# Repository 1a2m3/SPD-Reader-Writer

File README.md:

# SPD-RW
Arduino-based SPD Reader/Writer with Reversible Software Write Protection capabilities

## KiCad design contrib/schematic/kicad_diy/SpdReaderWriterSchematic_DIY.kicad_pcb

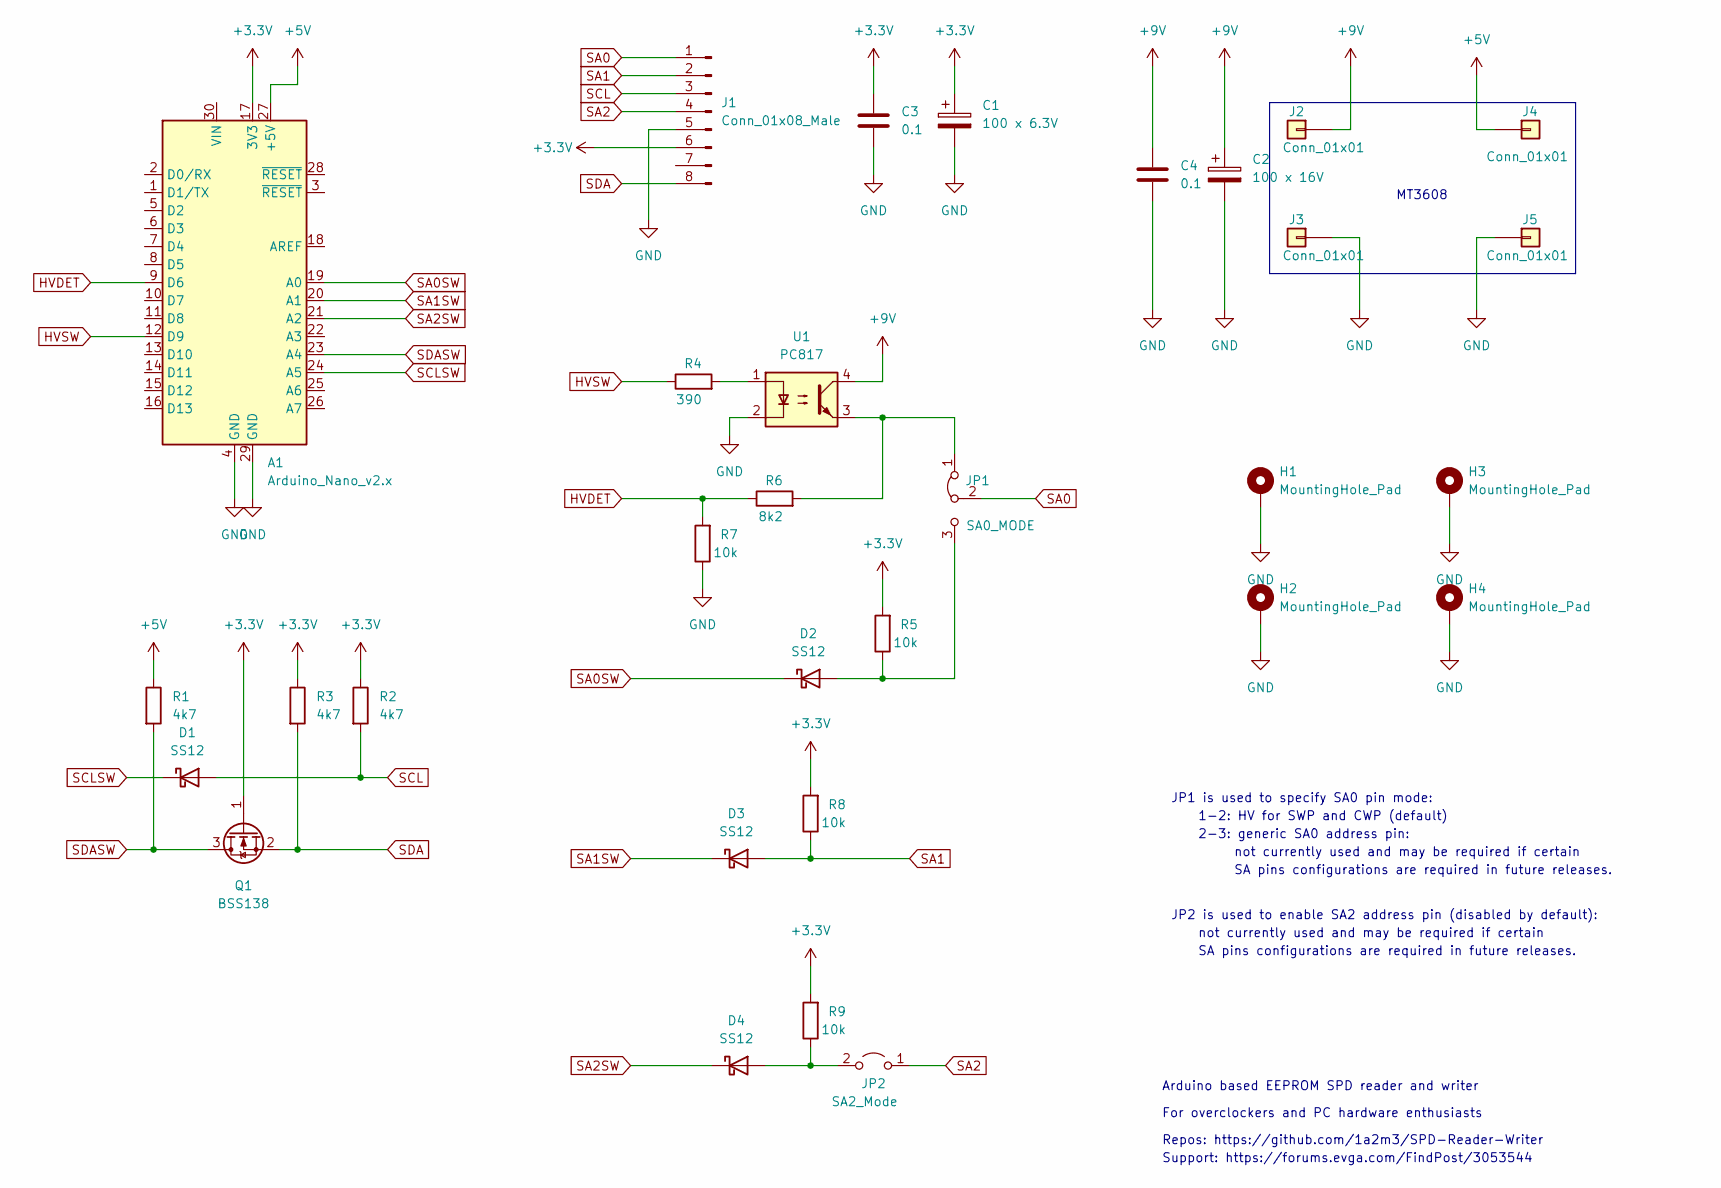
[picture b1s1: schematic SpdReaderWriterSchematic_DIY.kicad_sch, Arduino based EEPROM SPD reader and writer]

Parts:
A1: Arduino_Nano_v2.x; Arduino_Nano
C1: 100 x 6.3V; CP_Radial_D5.0mm_P2.00mm
C2: 100 x 16V; CP_Radial_D5.0mm_P2.00mm
C3, C4: 0.1; C_0805_2012Metric
D1, D2, D3, D4: SS12; D_SMA
H1, H2, H3, H4: MountingHole_Pad; MountingHole_3.2mm_M3_Pad
J1: Conn_01x08_Male; PinHeader_1x08_P2.54mm_Vertical
J2, J3, J4, J5: Conn_01x01; Pin_D1.0mm_L10.0mm_LooseFit
JP1: SA0_MODE; PinHeader_1x03_P2.54mm_Vertical
JP2: SA2_Mode; PinHeader_1x02_P2.54mm_Vertical
Q1: BSS138; SOT-23
R1, R2, R3: 4k7; R_0805_2012Metric
R4: 390; R_0805_2012Metric
R5: 10k; R_1206_3216Metric
R6: 8k2; R_0805_2012Metric
R7, R8, R9: 10k; R_0805_2012Metric
U1: PC817; DIP-4_W7.62mm

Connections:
+3.3V: A1.17 (3V3), C1.1, C3.1, J1.6, Q1.1 (G), R2.1, R3.1, R5.2, R8.2, R9.2
+5V: A1.27 (+5V), J4.1, R1.1
+9V: C2.1, C4.1, J2.1, U1.4
GND: A1.4 (GND), A1.29 (GND), C1.2, C2.2, C3.2, C4.2, H1.1, H2.1, H3.1, H4.1, J1.5, J3.1, J5.1, R7.1, U1.2
HVDET: A1.9 (D6), R6.1, R7.2
HVSW: A1.12 (D9), R4.1
unnamed: D2.2 (A), JP1.3 (B), R5.1
unnamed: D4.2 (A), JP2.2 (B), R9.1
unnamed: JP1.1 (A), R6.2, U1.3
unnamed: R4.2, U1.1
SA0: J1.1, JP1.2 (C)
SA0SW: A1.19 (A0), D2.1 (K)
SA1: D3.2 (A), J1.2, R8.1
SA1SW: A1.20 (A1), D3.1 (K)
SA2: J1.4, JP2.1 (A)
SA2SW: A1.21 (A2), D4.1 (K)
SCL: D1.2 (A), J1.3, R2.2
SCLSW: A1.24 (A5), D1.1 (K)
SDA: J1.8, Q1.2 (S), R3.2
SDASW: A1.23 (A4), Q1.3 (D), R1.2

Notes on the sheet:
JP2 is used to enable SA2 address pin (disabled by default):
MT3608
not currently used and may be required if certain
SA pins configurations are required in future releases.
1-2: HV for SWP and CWP (default)
Arduino based EEPROM SPD reader and writer
2-3: generic SA0 address pin:
Repos: https://github.com/1a2m3/SPD-Reader-Writer
Support: https://forums.evga.com/FindPost/3053544
For overclockers and PC hardware enthusiasts
JP1 is used to specify SA0 pin mode:

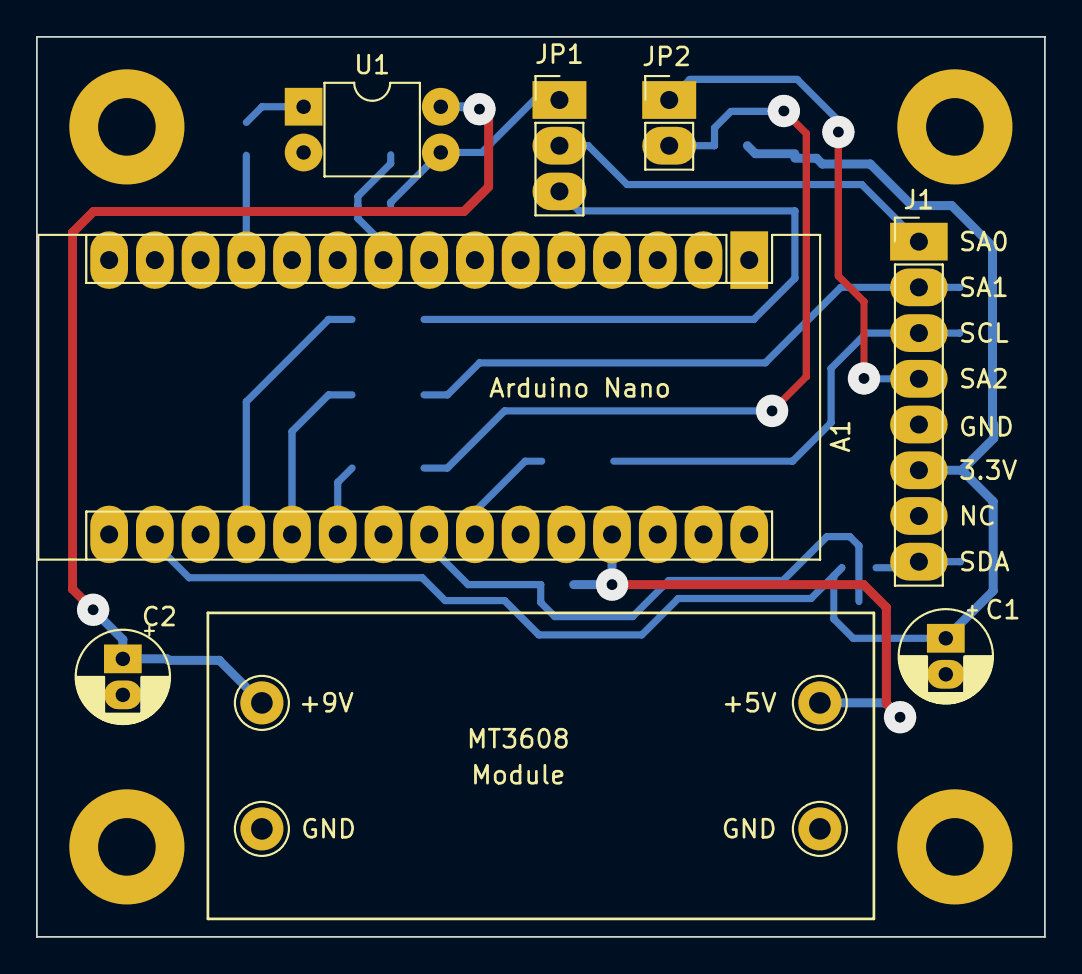
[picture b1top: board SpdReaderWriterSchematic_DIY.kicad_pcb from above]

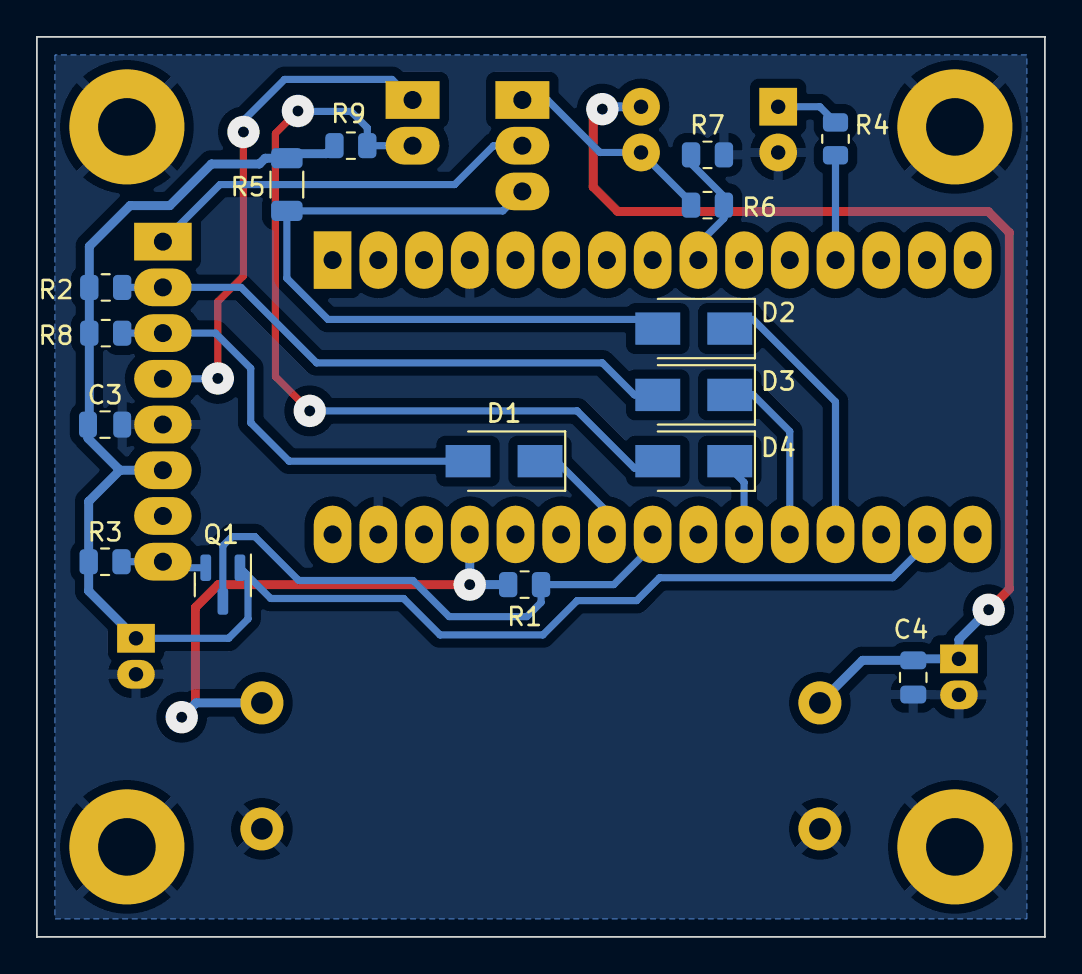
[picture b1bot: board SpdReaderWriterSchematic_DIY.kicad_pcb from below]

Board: 2 copper layers, 56.0 x 50.0 mm, 31 parts (16 on the bottom side), 20 nets.

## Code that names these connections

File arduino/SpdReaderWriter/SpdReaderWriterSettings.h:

#define PORT      Serial   // Communications Port, default is "Serial". Change to "SerialUSB" for native USB Arduinos (Leonardo, Micro, Due, Yun, etc)
#define BAUD_RATE 115200   // Serial port baud rate, must match program's serial baud rate
#define HVSW      6        // High Voltage (Optocoupler) switch pin number
#define SA0SW     2        // SA0 select pin number
#define SA1SW     3        // SA1 select pin number
#define SA2SW     4        // SA2 select pin number

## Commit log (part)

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2022-11-09 Formatting
2022-11-09 Byte array search
2022-11-09 GUI Screenshot
    New editor
2022-11-10 Cleanup
    LINQ looks cleaner :)
2022-11-10 SPD update
2022-11-10 SPD5 info and checks
2022-11-10 FW cleanup
    Firmware cleanup and update
2022-11-10 ID database update
    Jedec Manufacturers' IDs database update
2022-11-18 Compiler fix
    Fixed compiler to include SPD classes
2022-11-20 Smbus and driver improvements
    Improved Smbus and driver performance, cleanup
2022-12-09 Cleanup
2022-12-09 Improved stability
2022-12-15 Driver refactoring
2022-12-15 Cleanup and refactoring
2022-12-15 Added trim byte array + refactoring
2022-12-15 SPD refactoring, cleanup
    Crc validation, data types refactoring, cleanup
2022-12-15 File location fix
2022-12-19 Refactor, cleanup
2022-12-19 Alert updates
2022-12-19 SPD refactoring, cleanup, CRC updates
2022-12-19 P/N cleanup, Id fix
2022-12-21 Byte array and gzip updates
    Added byte array compare, gzip peek and performance improvements
2022-12-21 FW version info, refactoring
    Added included FW version info, refactoring and cleanup
2022-12-27 Array functions
2022-12-27 Compatibility update, cleanup
2022-12-27 AMD Expo CRC
    Added AMD Expo CRC validation
2022-12-28 Encoding
    Removed UTF-8 BOM
2022-12-30 Validation
    Data length validation
2022-12-30 Cleanup + Expo
    Added AMD Expo signature, some cleanup
2022-12-30 Cleanup
    Cleanup, added WP description
2022-12-30 Compatibility and performance
    Linq is slower for large file comparison, thus is gone
2022-12-30 Added length and P/N
    Added length and Part Number types
2022-12-30 Performance and cleanup
2022-12-30 Fixed compiler warnings
2023-01-01 New screenshot
2023-01-03 More cleanup
    Code decluttering, thanks to generics
2023-01-04 Refactoring, cleanup
2023-01-06 Data refactoring
2023-01-06 Driver behavior fixed
    Fixes driver extracting when running as normal user, and driver not stopping on exit.
2023-01-09 Improved reliability
2023-01-09 DDR5 RSWP
2023-01-13 Fixed DDR5 info
    Fixed DDR5 SPD manufacturer name detection
2023-01-13 Arrays, cleanup
2023-01-14 SPD5 hub & DDR5 support, cleanup
2023-01-14 Refactoring and cleanup
2023-01-14 Compatibility, checks, branding
2023-01-14 Array contains method
2023-01-14 Cleanup and color option
2023-01-14 Fixed warnings
    Fixed warnings CS0660 and CS0661
2023-01-15 Improvements and smbus fix
    Improved reading performance, fixed smbus bus # bug, added smbus exceptions, code cleanup
2023-01-15 Block check
2023-01-16 Improved performance
2023-01-16 Refactoring
2023-01-19 Cleanup, Alert time
2023-01-19 Name, cleanup
2023-01-19 Array functions, cleanup
2023-01-19 FW check, cleanup
2023-01-19 Subarray
2023-01-20 Path and switches compatibility
    File path and output modifier switches compatibility
2023-01-20 Scan fix
2023-01-25 DDR5 support
2023-01-25 Update RSWP on hot swap
2023-01-26 Outdated schematic
2023-01-26 Write protection improvement
    improved RSWP tests
2023-01-27 Pin config, cleanup
2023-01-28 Generics, cleanup
2023-01-31 Performance, protocol, cleanup
    Improved performance, added new protocol support, added generics, cleanup
2023-01-31 Refactoring
    Moved SpdReaderWriterDll to SpdReaderWriterCore namespace
2023-02-02 Better performance and stability
    Improved performance and stability, cleanup, and refactoring
2023-02-02 Byte array to hex string
2023-02-02 20230202 screenshot
    Version 20230202 screenshot showing DDR5 support
2023-02-03 EEPROM page set fix
2023-02-03 Improved spd size
2023-02-03 Improved performance and stability
2023-02-05 DDR5 test
2023-02-05 DDR5 support, protocol update
2023-02-05 Updated FW
2023-02-05 Improved stability, added DDR5 support
2023-03-09 Fixes inaccessible smbus on some systems
2023-03-09 Improved performance and reliability
2023-05-06 Object array, cleanup
2023-05-06 Pci info
2023-05-06 Intel 600/700 support
2023-05-06 Write test, Cleanup
2023-06-09 WP compatibility
    Write protection compatibility update for SDR-DDR4
2023-08-05 Smbus DDR5 RSWP support
    Added Smbus DDR5 RSWP detection
2023-09-14 Update Data.cs
    Updated object array converter to support nested arrays
2023-09-14 Update Data.cs
    One numeric data check
2023-09-14 Update Data.cs
    Fix for nested arrays
2023-09-15 Update Arduino.cs
    Refactoring, SPD5 hub RSWP verification
2023-09-19 Extended BDC functions + fixed CompareArray()
    Extended BDC functions to work with any type of numeric input;
    Added array size check to CompareArray
2023-09-19 Removed WinRing0 files
2023-09-23 Data size, fixed BCD
2023-09-23 Hardware IDs enums
2023-09-23 Total refactoring
2023-09-23 Not needed
2023-09-23 SPD5 hub write verification
2023-09-24 Memory read, cleanup
2023-09-24 Driver & Firmware updated
    Replaced WinRing0 driver with CPUID CPUZ driver
2023-09-24 Cleanup
    Removed unused device
2023-09-24 Improved write protection test
2023-09-24 Cleanup :)
    That
    extra
    line
    bothered
    me
2023-09-27 Added CloseHandle
2023-09-27 Improved stability and performance
2023-09-29 Refactoring for consistency
2023-09-29 Process and assembly name
2023-09-29 Cleanup, error codes
2023-09-30 Improved stability, cleanup
2023-09-30 Fixed access modifiers
2023-10-12 Cleanup
    removed cpuz driver files
2023-10-12 Improved AMD smbus detection
2023-10-29 Cleanup, refactoring
2023-11-01 Improved random arrays
2023-11-18 Vendor ID DB update
    ID codes database update (ref. JEP106BH, Sept 2023)
2023-12-02 added VIA smbus, refactoring
    Added VIA chipsets smbus support
2023-12-05 VIA updates
    Improved VIA smbus support
2023-12-05 Protocol update, cleanup
2023-12-05 ASCII updates
2023-12-05 P/N checks
2023-12-05 Compatibility update
2023-12-06 X299 fix
    fix for Skylake-X smbus
2023-12-06 protocol update, improved ddr5 compatibility
2023-12-08 Added baud rate option, improved stability
2023-12-08 PMIC validation, cleanup
2023-12-08 FW update
    ver 20231207
2023-12-08 pmic address validation
2023-12-08 X299 smbus status + general cleanup
2023-12-08 exe assembly version
2023-12-08 Help & input validation
    Updated help, improved user input validation
2023-12-08 port validation
2023-12-08 Admin, versions updates
2023-12-09 device interface
2023-12-09 dll versions
2023-12-09 screenshots
2023-12-09 new screenshots
    New screenshots showing Arduino and Smbus sessions
2023-12-09 via smbus fix
    Fixed VIA smbus for legacy chipsets
2023-12-10 arduino connection and address check
2023-12-10 nforce busy status
2023-12-13 Missed release commits
    Changes I forgot to commit that made it into the release
2023-12-15 Improved DDR5 detection
2023-12-16 find arduino baud rate parameter
    added baud rate parameter to find arduino command
2023-12-19 Move refactoring
2023-12-19 Performance + split and move refactoring
    Split kernel and driver classes, refactoring, smbus performance improvements
2023-12-21 Refactoring + rename
2023-12-23 Improved stability, cleanup
    improved driver removal process and formatting
2024-01-22 Improved name handling, eeprom commands
2024-01-28 Fixed addressing, added eeprom command
2024-02-25 Refactoring & cleanup
2024-03-04 Renamed PCI class
    PciDevice > PciConfig
2024-03-04 Hex to Number, Struct to byte array, and Mutex functions added
    Added hex string to number validation and conversion function; struct to byte array and vice versa converters; and mutex creation, locking, and unlocking functions.
2024-03-05 Improved stability, refactoring
2024-03-07 Added DataFile structure
2024-03-07 VIA update
2024-03-07 Cleanup + refactoring
2024-03-08 Hex string validation, convert refactoring
2024-03-08 Improved performance & stability
2024-03-10 EEPROM read, find overload; cleanup
2024-03-10 ddr4 detect validation, formatting
2024-03-12 Move + Refactoring
2024-03-13 Refactoring, performance, smbus clear block rswp
2024-03-16 Refactoring, version info
2024-03-16 renamed
2024-03-16 String format
2024-03-19 String to number, consecutive array overload
2024-03-19 Pci, Io, Mem read added, refactoring, cleanup
2024-03-20 Bytes to hex, shuffle, swap
    Bytes to hex string; shuffle array, swap two items
2024-03-22 Improved stability and compatibility
2024-03-23 ArrayContains overloads, UniqueArray, cleanup
2024-03-23 Improved stability, write test reliability, refactoring
2024-03-24 Improved performance, refactoring
2024-03-25 Alternative "all" address parameter, fixed pswp, refactoring
2024-03-25 Improved performance, cleanup
2024-03-27 Bitmask match added
